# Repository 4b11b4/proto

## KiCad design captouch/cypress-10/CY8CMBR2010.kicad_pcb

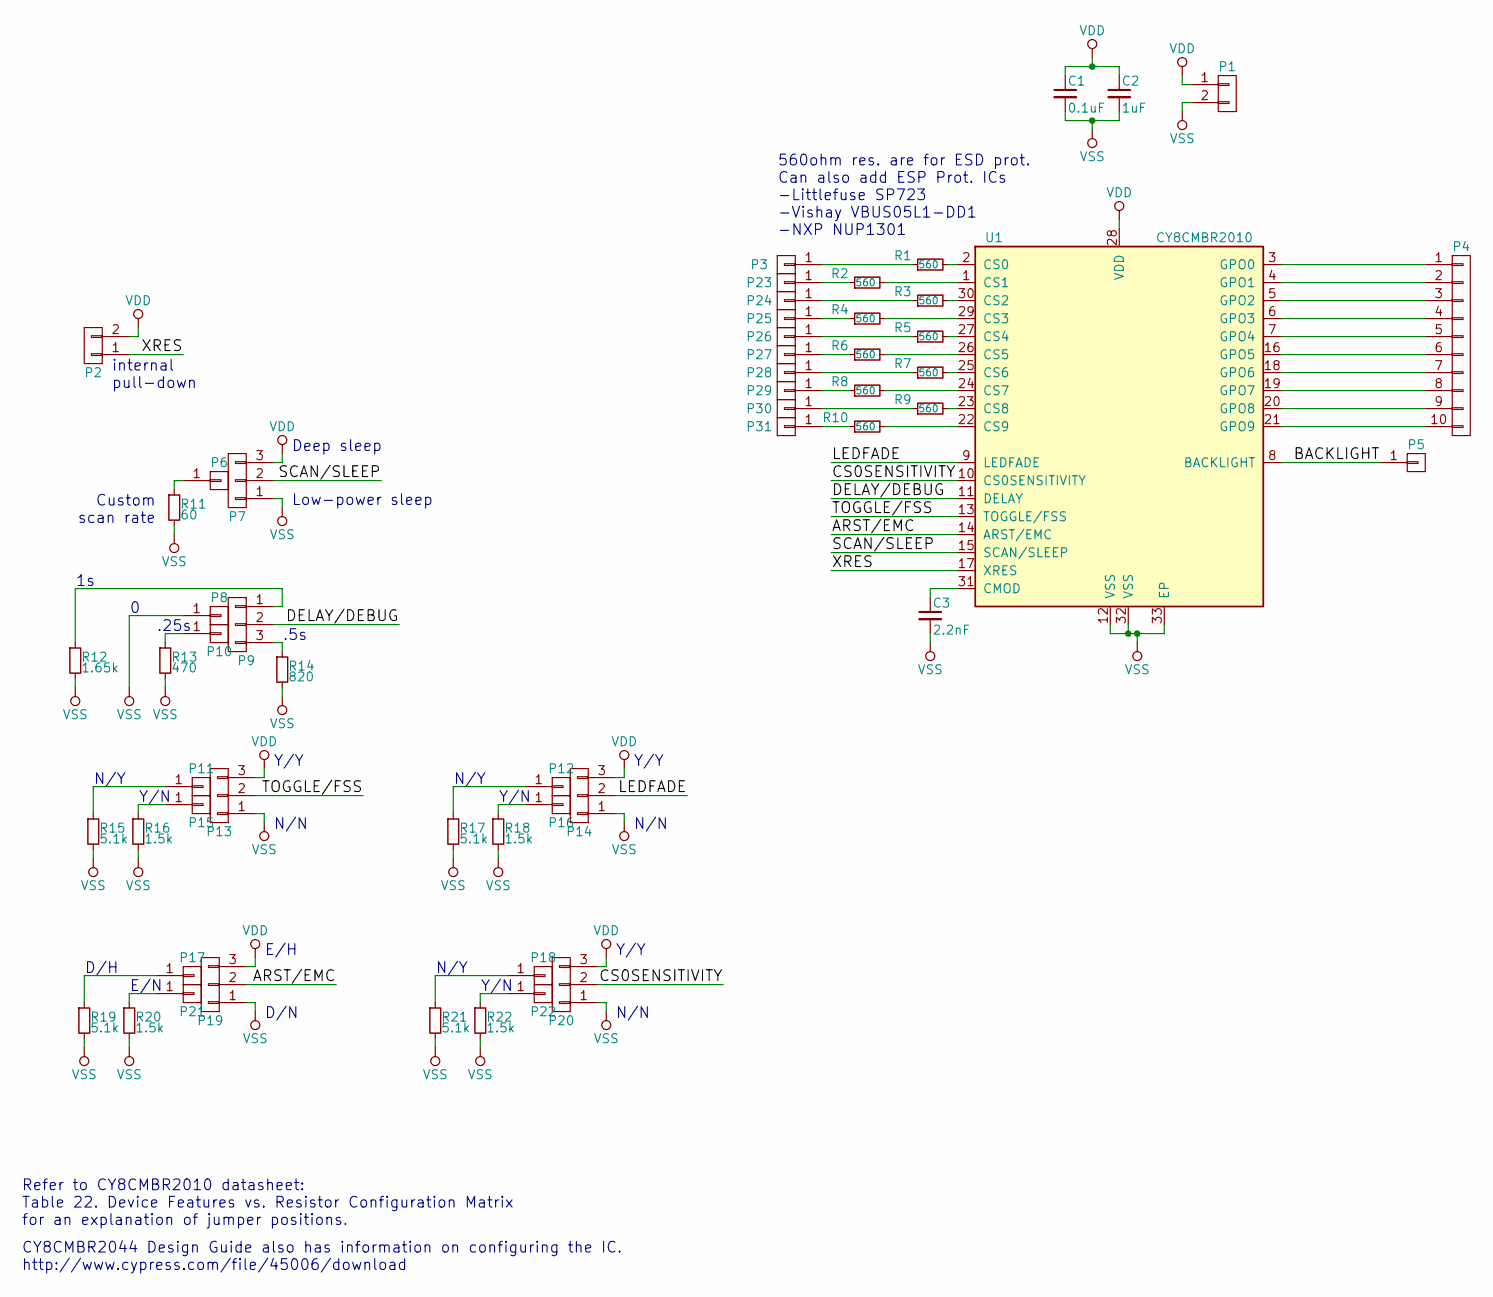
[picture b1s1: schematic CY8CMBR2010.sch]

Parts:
C1: 0.1uF; C_1206_HandSoldering
C2: 1uF; C_1206_HandSoldering
C3: 2.2nF; C_0603_HandSoldering; Mfr Part # GRM1885C1H222JA01D
P1, P2: CONN_01X02; Pin_Header_Straight_1x02
P3, P5, P6, P8, P10, P11, P12, P15, P16, P17, P18, P21, P22, P23, P24, P25, P26, P27, P28, P29, P30, P31: CONN_01X01; Pin_Header_Straight_1x01
P4: CONN_01X10; Pin_Header_Straight_1x10
P7, P9, P13, P14, P19, P20: CONN_01X03; Pin_Header_Straight_1x03
R1, R2, R3, R4, R5, R6, R7, R8, R9, R10: 560; R_1206_HandSoldering
R11: 60; R_1206_HandSoldering
R12: 1.65k; R_1206_HandSoldering
R13: 470; R_1206_HandSoldering
R14: 820; R_1206_HandSoldering
R15, R17, R19, R21: 5.1k; R_1206_HandSoldering
R16, R18, R20, R22: 1.5k; R_1206_HandSoldering
U1: CY8CMBR2010; QFN-32-1EP_5x5mm_Pitch0.5mm_4b11b4; Mfr Part # CY8CMBR2010-24LQXI

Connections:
/ARST/EMC: P19.2, U1.14 (ARST/EMC)
/BACKLIGHT: P5.1, U1.8 (BACKLIGHT)
/CS0SENSITIVITY: P20.2, U1.10 (CS0SENSITIVITY)
/DELAY/DEBUG: P9.2, U1.11 (DELAY)
/LEDFADE: P14.2, U1.9 (LEDFADE)
/SCAN/SLEEP: P7.2, U1.15 (SCAN/SLEEP)
/TOGGLE/FSS: P13.2, U1.13 (TOGGLE/FSS)
/XRES: P2.1, U1.17 (XRES)
unnamed: C3.1, U1.31 (CMOD)
unnamed: P3.1, R1.1
unnamed: P4.1, U1.3 (GPO0)
unnamed: P4.2, U1.4 (GPO1)
unnamed: P4.3, U1.5 (GPO2)
unnamed: P4.4, U1.6 (GPO3)
unnamed: P4.5, U1.7 (GPO4)
unnamed: P4.6, U1.16 (GPO5)
unnamed: P4.7, U1.18 (GPO6)
unnamed: P4.8, U1.19 (GPO7)
unnamed: P4.9, U1.20 (GPO8)
unnamed: P4.10, U1.21 (GPO9)
unnamed: P6.1, R11.1
unnamed: P9.1, R12.1
unnamed: P9.3, R14.1
unnamed: P10.1, R13.1
unnamed: P11.1, R15.1
unnamed: P12.1, R17.1
unnamed: P15.1, R16.1
unnamed: P16.1, R18.1
unnamed: P17.1, R19.1
unnamed: P18.1, R21.1
unnamed: P21.1, R20.1
unnamed: P22.1, R22.1
unnamed: P23.1, R2.1
unnamed: P24.1, R3.1
unnamed: P25.1, R4.1
unnamed: P26.1, R5.1
unnamed: P27.1, R6.1
unnamed: P28.1, R7.1
unnamed: P29.1, R8.1
unnamed: P30.1, R9.1
unnamed: P31.1, R10.1
unnamed: R1.2, U1.2 (CS0)
unnamed: R2.2, U1.1 (CS1)
unnamed: R3.2, U1.30 (CS2)
unnamed: R4.2, U1.29 (CS3)
unnamed: R5.2, U1.27 (CS4)
unnamed: R6.2, U1.26 (CS5)
unnamed: R7.2, U1.25 (CS6)
unnamed: R8.2, U1.24 (CS7)
unnamed: R9.2, U1.23 (CS8)
unnamed: R10.2, U1.22 (CS9)
VDD: C1.1, C2.1, P1.1, P2.2, P7.3, P13.3, P14.3, P19.3, P20.3, U1.28 (VDD)
VSS: C1.2, C2.2, C3.2, P1.2, P7.1, P8.1, P13.1, P14.1, P19.1, P20.1, R11.2, R12.2, R13.2, R14.2, R15.2, R16.2, R17.2, R18.2, R19.2, R20.2, R21.2, R22.2, U1.12 (VSS), U1.32 (VSS), U1.33 (EP)

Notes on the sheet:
CY8CMBR2044 Design Guide also has information on configuring the IC. http://www.cypress.com/file/45006/download
Y/Y
N/N
N/Y
Y/N
.25s
Low-power sleep
Deep sleep
Custom scan rate
.5s
internal pull-down
560ohm res. are for ESD prot. Can also add ESP Prot. ICs -Littlefuse SP723 -Vishay VBUS05L1-DD1 -NXP NUP1301
E/H
D/N
D/H
E/N
Refer to CY8CMBR2010 datasheet: Table 22. Device Features vs. Resistor Configuration Matrix for an explanation of jumper positions.

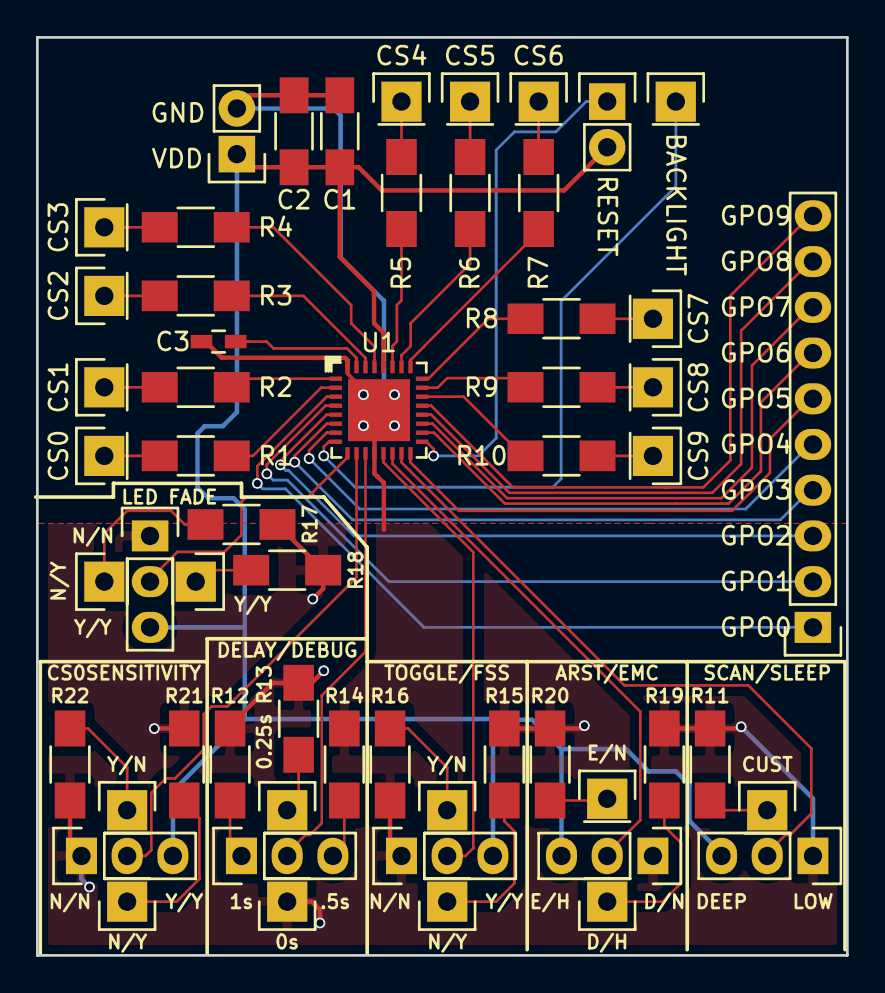
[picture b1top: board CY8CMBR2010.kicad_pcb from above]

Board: 2 copper layers, 45.0 x 51.0 mm, 57 parts (0 on the bottom side), 53 nets.

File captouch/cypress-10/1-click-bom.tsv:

References	Qty	Description
C1	1	C Small 0.1uF 1206 HandSoldering
C2	1	C Small 1uF 1206 HandSoldering
C3	1	C Small 2.2nF 0603 HandSoldering
P1, P2	2	CONN 01X02 Pin Header Straight 1x02
P4	1	CONN 01X10 Pin Header Straight 1x10
P11, P15, P8, P10, P6, P17, P21, P18, P22, P12, P16, P5, P3, P23, P24, P25, P26, P27, P28, P29, P30, P31	22	CONN 01X01 Pin Header Straight 1x01
P13, P9, P7, P19, P20, P14	6	CONN 01X03 Pin Header Straight 1x03
R1, R2, R3, R5, R7, R9, R10, R8, R6, R4	10	R Small 560 1206 HandSoldering
R11	1	R Small 60 1206 HandSoldering
R12	1	R Small 1.65k 1206 HandSoldering
R13	1	R Small 470 1206 HandSoldering
R14	1	R Small 820 1206 HandSoldering
R15, R19, R21, R17	4	R Small 5.1k 1206 HandSoldering
R16, R20, R22, R18	4	R Small 1.5k 1206 HandSoldering
U1	1	CY8CMBR2010 QFN-32-1EP 5x5mm Pitch0.5mm 4b11b4

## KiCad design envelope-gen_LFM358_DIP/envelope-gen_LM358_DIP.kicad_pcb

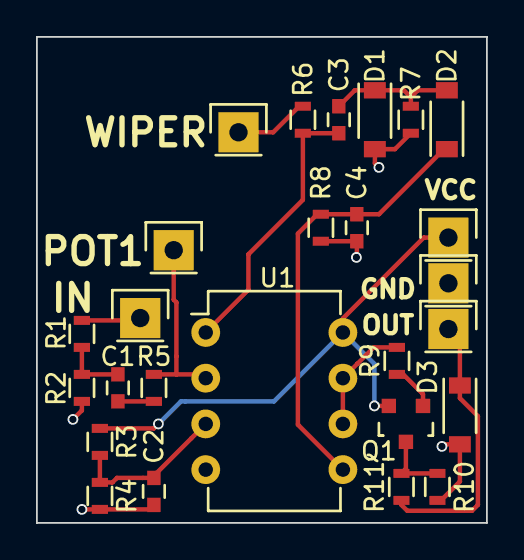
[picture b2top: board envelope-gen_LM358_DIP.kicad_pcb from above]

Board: 2 copper layers, 25.0 x 27.0 mm, 26 parts (0 on the bottom side), 15 nets.

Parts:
C1, C3: 0.22uF; C_0603
C2: 10uF; C_0603
C4: 1uF; C_0603
D1, D2: 1N4148; SOD-123
D3: 5.1V; SOD-123
P1, P2, P3, P4, P5, P6: CONN_01X01; Pin_Header_Straight_1x01
Q1: MMBT3904; SOT-23
R1, R2, R3, R4, R7, R10: 10k; R_0603
R5, R6, R9: 1k; R_0603
R8: 100k; R_0603
R11: 220; R_0603
U1: LM358; DIP-8_W7.62mm

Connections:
/IN: P2.1, R1.1
/OUT: D3.1, P4.1, R11.2
/POT1: P5.1, R5.1, U1.2
/VCC: P3.1, Q1.2, R3.1, U1.8
/WIPER: P6.1, R6.2
GND: C2.2, C4.1, D1.2, D3.2, P1.1, R2.2, R4.2, R7.2, R8.2, R10.2, U1.4
unnamed: C1.1, R5.2
unnamed: C1.2, R1.2, R2.1
unnamed: C2.1, R3.2, R4.1, U1.3
unnamed: C3.1, D1.1, D2.2, R7.1
unnamed: C3.2, R6.1, U1.1
unnamed: C4.2, D2.1, R8.1, U1.5
unnamed: Q1.1, R9.1
unnamed: Q1.3, R10.1, R11.1
unnamed: R9.2, U1.6, U1.7

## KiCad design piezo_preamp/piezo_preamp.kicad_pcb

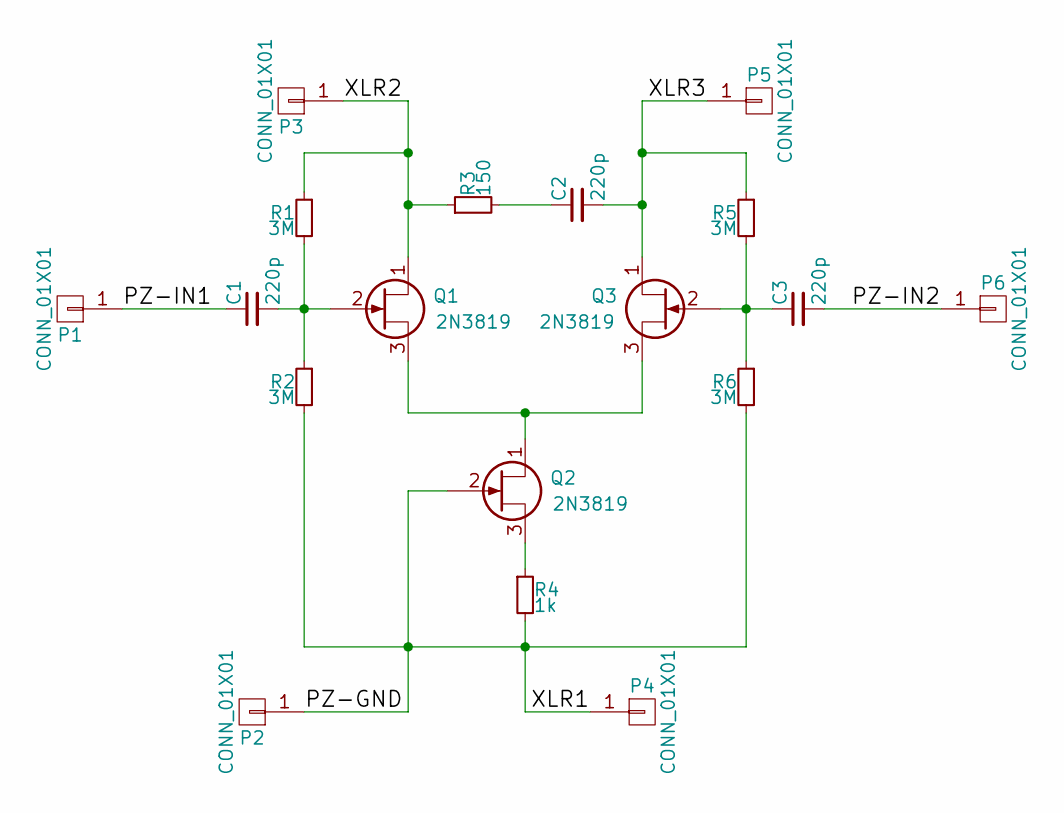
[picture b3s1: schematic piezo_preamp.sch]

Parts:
C1, C2, C3: 220p; C_0805; Mfr Part No CC0805JRNPO9BN221
P1, P2, P3, P4, P5, P6: CONN_01X01; Pin_Header_Straight_1x01
Q1, Q2, Q3: 2N3819; TO-92_Inline_Narrow_Oval; Mfr Part No 2N3819
R1, R2, R5, R6: 3M; R_0805; Mfr Part No RC0805FR-073ML
R3: 150; R_0805; Mfr Part No RC0805FR-07150RL
R4: 1k; R_0805; Mfr Part No RC0805FR-071KL

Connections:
/PZ-GND: P2.1, P4.1, Q2.2 (G), R2.2, R4.2, R6.2
/PZ-IN1: C1.1, P1.1
/PZ-IN2: C3.2, P6.1
/XLR2: P3.1, Q1.1 (D), R1.1, R3.1
/XLR3: C2.2, P5.1, Q3.1 (D), R5.1
unnamed: C1.2, Q1.2 (G), R1.2, R2.1
unnamed: C2.1, R3.2
unnamed: C3.1, Q3.2 (G), R5.2, R6.1
unnamed: Q1.3 (S), Q2.1 (D), Q3.3 (S)
unnamed: Q2.3 (S), R4.1

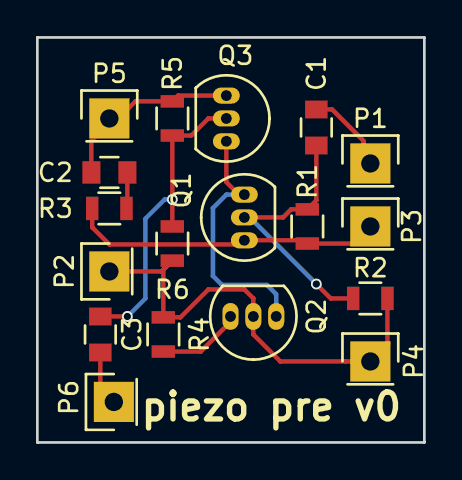
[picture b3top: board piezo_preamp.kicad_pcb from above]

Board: 2 copper layers, 21.5 x 22.5 mm, 18 parts (0 on the bottom side), 10 nets.

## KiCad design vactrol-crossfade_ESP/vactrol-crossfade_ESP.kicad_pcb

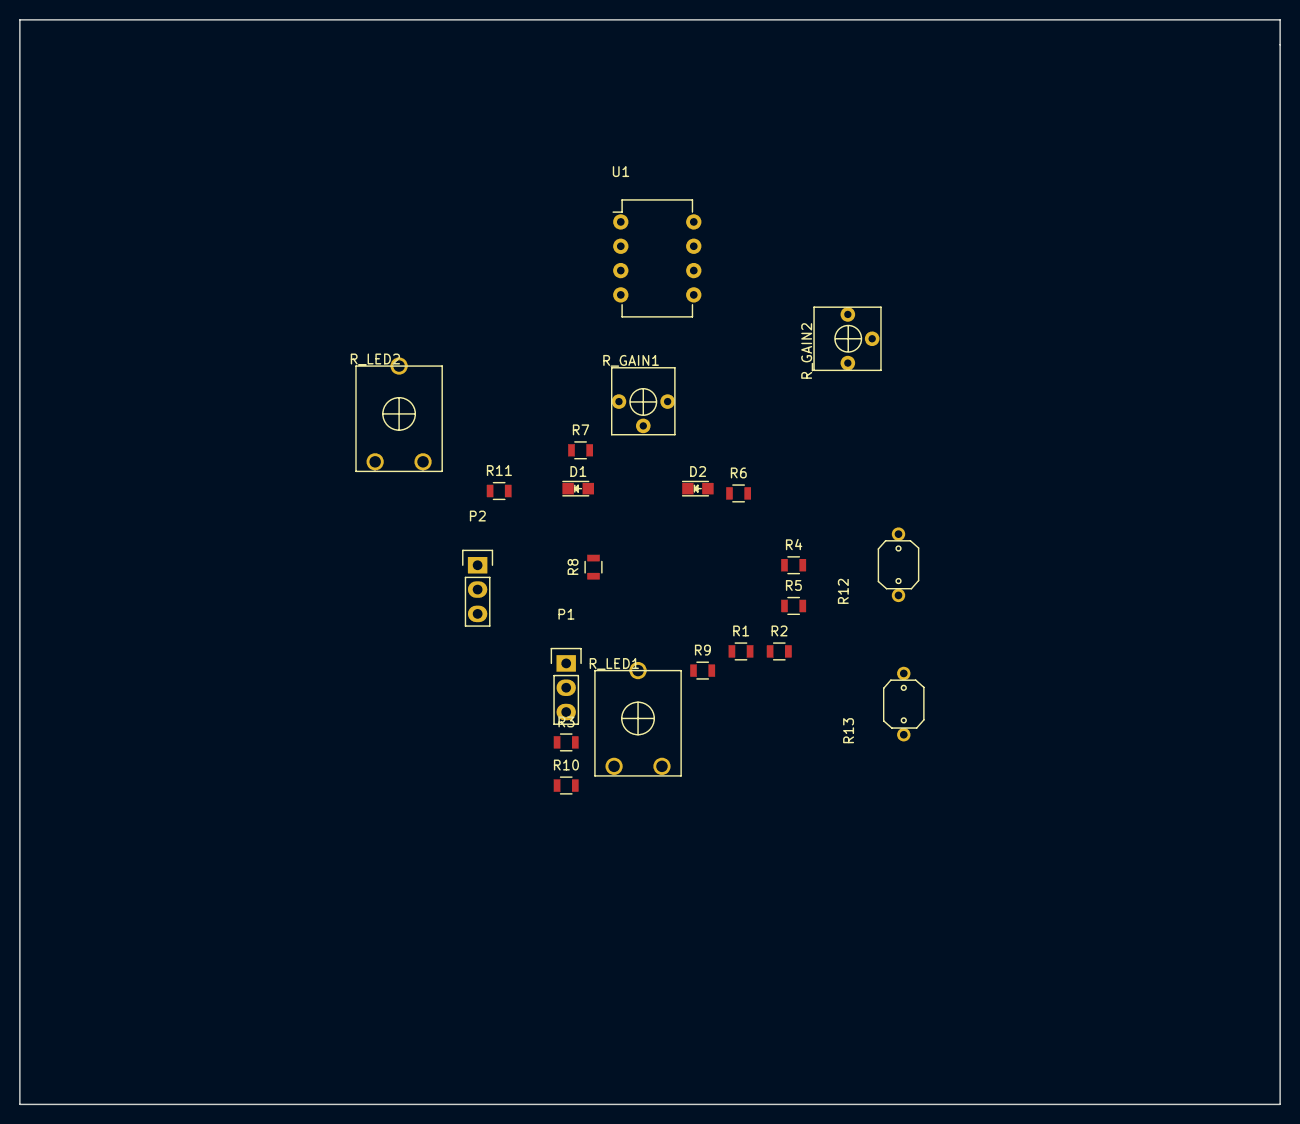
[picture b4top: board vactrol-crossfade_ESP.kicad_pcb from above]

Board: 2 copper layers, 131.6 x 113.3 mm, 22 parts (0 on the bottom side), 19 nets, no tracks yet.

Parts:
D1, D2: Red; LED_0805
P1, P2: CONN_01X03; Pin_Header_Straight_1x03
R1, R2, R8, R9: 100k; R_0805
R3: 1k; R_0805
R4, R5, R6, R7: 10k; R_0805
R10, R11: 270; R_0805
R12, R13: Photores; Photocell_5528CDS
R_GAIN1, R_GAIN2: 100k; 3362P
R_LED1, R_LED2: POT; 3119P
U1: LM358; DIP-8_W7.62mm

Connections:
/CV: P1.2, R3.1
/IN1: P2.1, R12.1
/IN2: P2.3, R13.2
/INV: D2.2, R6.1, R9.2, U1.7
/NON-INV: D1.2, R7.1, R8.2, U1.1
/OUT: P2.2, R12.2, R13.1
/VREF: R1.1, R2.2, U1.2, U1.5
GND: R8.1, R9.1, R_LED1.2, R_LED2.2
unnamed: D1.1, R10.1
unnamed: D2.1, R11.1
unnamed: R3.2, R4.2, R5.2
unnamed: R4.1, R_GAIN1.2, U1.3
unnamed: R5.1, R_GAIN2.2, U1.6
unnamed: R6.2, R_GAIN2.1
unnamed: R7.2, R_GAIN1.1
unnamed: R10.2, R_LED1.1
unnamed: R11.2, R_LED2.1
VCC: P1.3, R1.2, U1.8
VEE: P1.1, R2.1, U1.4
